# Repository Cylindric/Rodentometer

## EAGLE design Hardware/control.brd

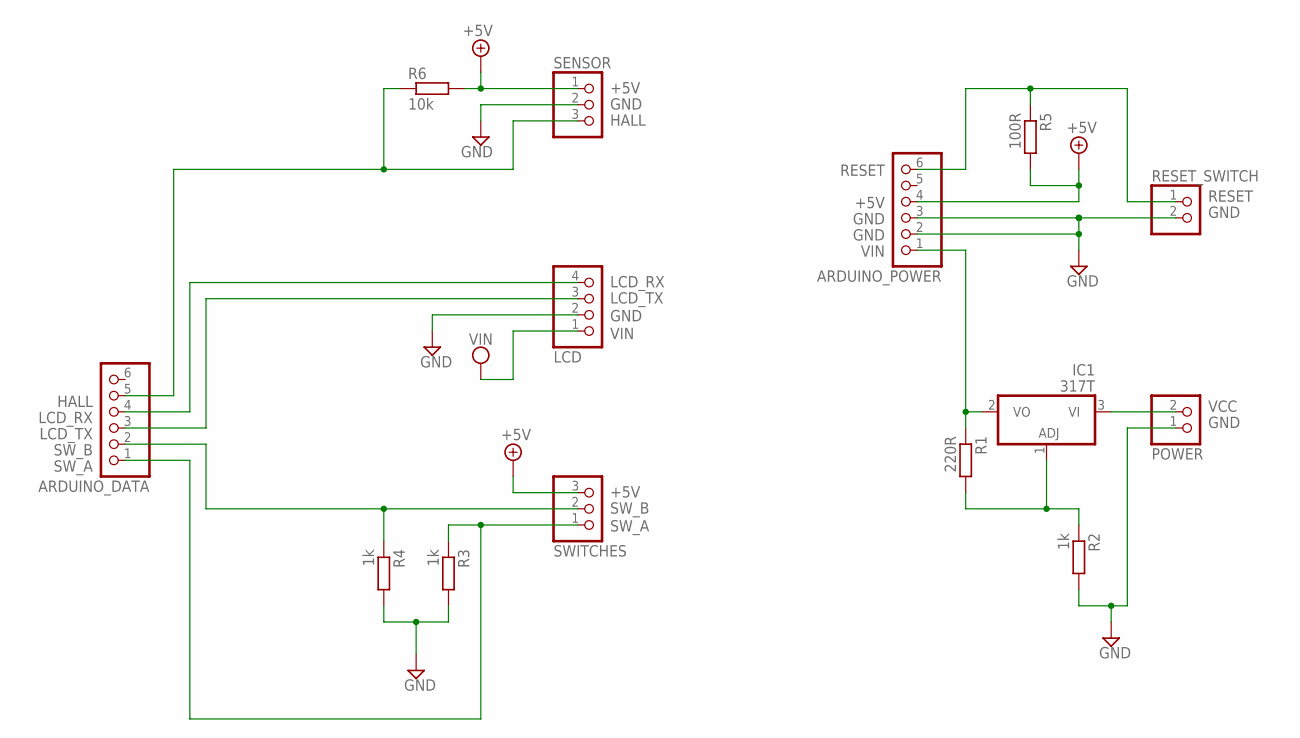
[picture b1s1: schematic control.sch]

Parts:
ARDUINO_DATA: PINHD-1X6; 1X06
ARDUINO_POWER: PINHD-1X6; 1X06
IC1: 317T; TO220H
LCD: PINHD-1X4; 1X04
POWER: PINHD-1X2; 1X02
R1: 220R; 0204/7
R2, R4: 1k; 0204/7
R3: 1k; 0207/10
R5: 100R; 0204/7
R6: 10k; 0207/7
RESET_SWITCH: PINHD-1X2; 1X02
SENSOR: PINHD-1X3; 1X03
SWITCHES: PINHD-1X3; 1X03

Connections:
+5V: ARDUINO_POWER.4, R5.2, R6.2, SENSOR.1, SWITCHES.3
GND: ARDUINO_POWER.2, ARDUINO_POWER.3, LCD.2, POWER.1, R2.2, R3.2, R4.2, RESET_SWITCH.2, SENSOR.2
HALL: ARDUINO_DATA.5, R6.1, SENSOR.3
LCD_RX: ARDUINO_DATA.4, LCD.4
LCD_TX: ARDUINO_DATA.3, LCD.3
unnamed: IC1.1 (ADJ), R1.2, R2.1
RESET: ARDUINO_POWER.6, R5.1, RESET_SWITCH.1
SW_A: ARDUINO_DATA.1, R3.1, SWITCHES.1
SW_B: ARDUINO_DATA.2, R4.1, SWITCHES.2
VCC: IC1.3 (VI), POWER.2
VIN: ARDUINO_POWER.1, IC1.2 (VO), LCD.1, R1.1

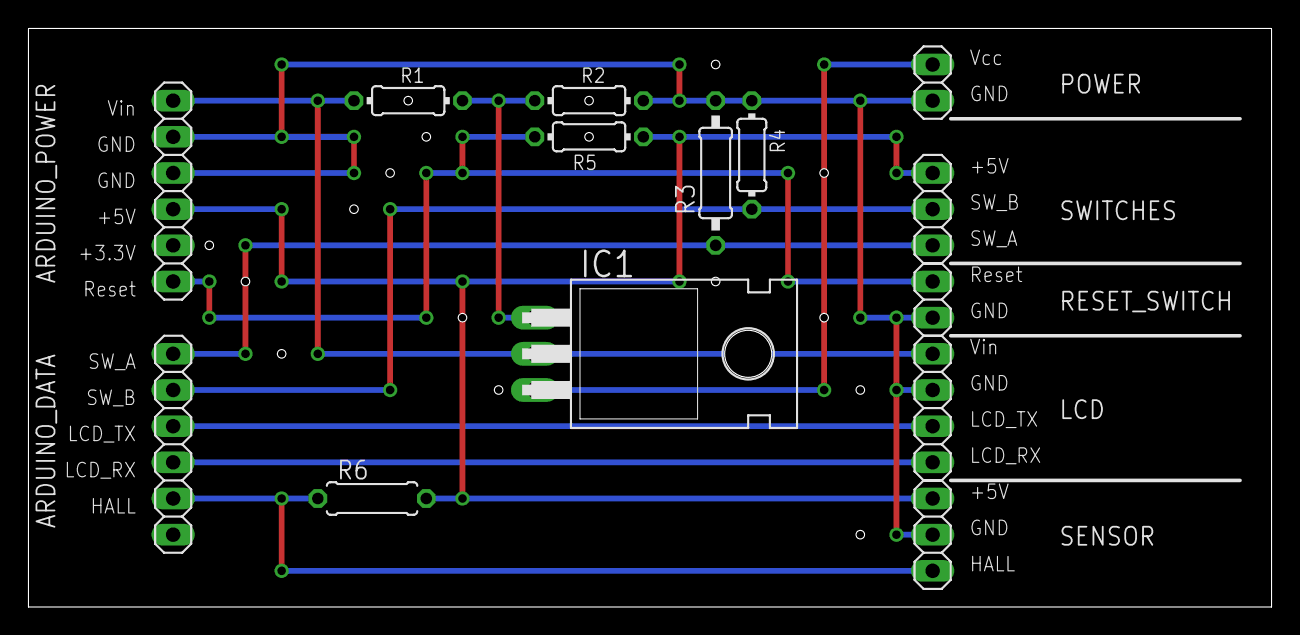
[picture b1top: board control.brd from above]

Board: 2 copper layers, 87.3 x 40.6 mm, 14 parts (0 on the bottom side), 11 nets.

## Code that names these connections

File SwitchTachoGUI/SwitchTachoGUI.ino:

#include <SoftwareSerial.h>
#include <SerialGLCD.h>
#include <Bounce.h>
#include "gui.h"

#define DEBUG
//#define TESTING

#ifdef DEBUG
  #define DEBUG_PRINT(x) Serial.print(x)
  #define DEBUG_PRINTLN(x) Serial.println(x)
#else
  #define DEBUG_PRINT(x)
  #define DEBUG_PRINTLN(x)
#endif

static const int MODE = 1; // Operation mode: 0=test, 1=sensor

static const int LCD_RX_PIN = 7; // Pin connected to LCD
static const int LCD_TX_PIN = 6; // Pin connected to LCD
static const int TOP_BUTTON_PIN = 9; // Pin connected to the top button
static const int BOTTOM_BUTTON_PIN = 8; // Pin connected to the bottom button
static const int SENSOR_PIN = 3; // Pin connected to the Hall sensor (interrupt pin)
static const int DEBOUNCE = 20; // Debounce filter time (ms)

static const int GUI_DELAY_MS = 40; // Delay between frames (ms)

GUI Gui(LCD_RX_PIN, LCD_TX_PIN);
Bounce TopButton(TOP_BUTTON_PIN, 5);
Bounce BottomButton(BOTTOM_BUTTON_PIN, 5);

volatile int revolutions = 0;
volatile long lastRevolutionTrigger = 0;
long lastFrameUpdate = 0;

void setup() 
{
  Serial.begin(115200);
  DEBUG_PRINTLN("Hello");
  delay(500);
  Gui.begin();
  attachInterrupt(1, SensorInterrupt, FALLING);
}


void loop() {
  if (MODE == 0) {
    TestLoop();
  } else {
    MainLoop();
  }
}


void TestLoop() 
{
  Gui.update(revolutions);
  revolutions = revolutions + random(0, 5);
}


void MainLoop() {
  TopButton.update();
  BottomButton.update();

#ifdef TESTING
  int reading = (random(100)>90);
#else
  int reading = digitalRead(SENSOR_PIN);
#endif

  if (TopButton.read()) {
    revolutions = 0;
    Gui.resetStatistics();
  }

  Gui.setButton(GUI::TOP_BUTTON, TopButton.read());
  Gui.setButton(GUI::BOTTOM_BUTTON, BottomButton.read());
  if (millis() - lastFrameUpdate > GUI_DELAY_MS) {
    Gui.update(revolutions);
    lastFrameUpdate = millis();
  }
}


void SensorInterrupt() {
  if (millis()-lastRevolutionTrigger > DEBOUNCE) {
    revolutions++;
    lastRevolutionTrigger = millis();
    digitalWrite(13, revolutions%2);
  }
}

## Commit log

2012-01-16 Added initial Arduino sketches
2012-01-19 Screen now works with new SerialGLCD
2012-01-19 Created a GUI
2012-01-20 some adjustments
2012-01-21 Testing out buttons
2012-01-22 Testing
2012-01-23 Added a datalogger
2012-01-23 Playing around with an Ethernet shield
2012-01-24 Pachube is updating
2012-01-24 Split Pachube into own class
2012-01-24 Moved config to own file
2012-01-27 Added some hardware plans
2012-01-29 Added some better schematics
2012-01-31 Fixed error in schematics and updated code to use Interrupt
2012-01-31 Added some screenshots ready for blogging
